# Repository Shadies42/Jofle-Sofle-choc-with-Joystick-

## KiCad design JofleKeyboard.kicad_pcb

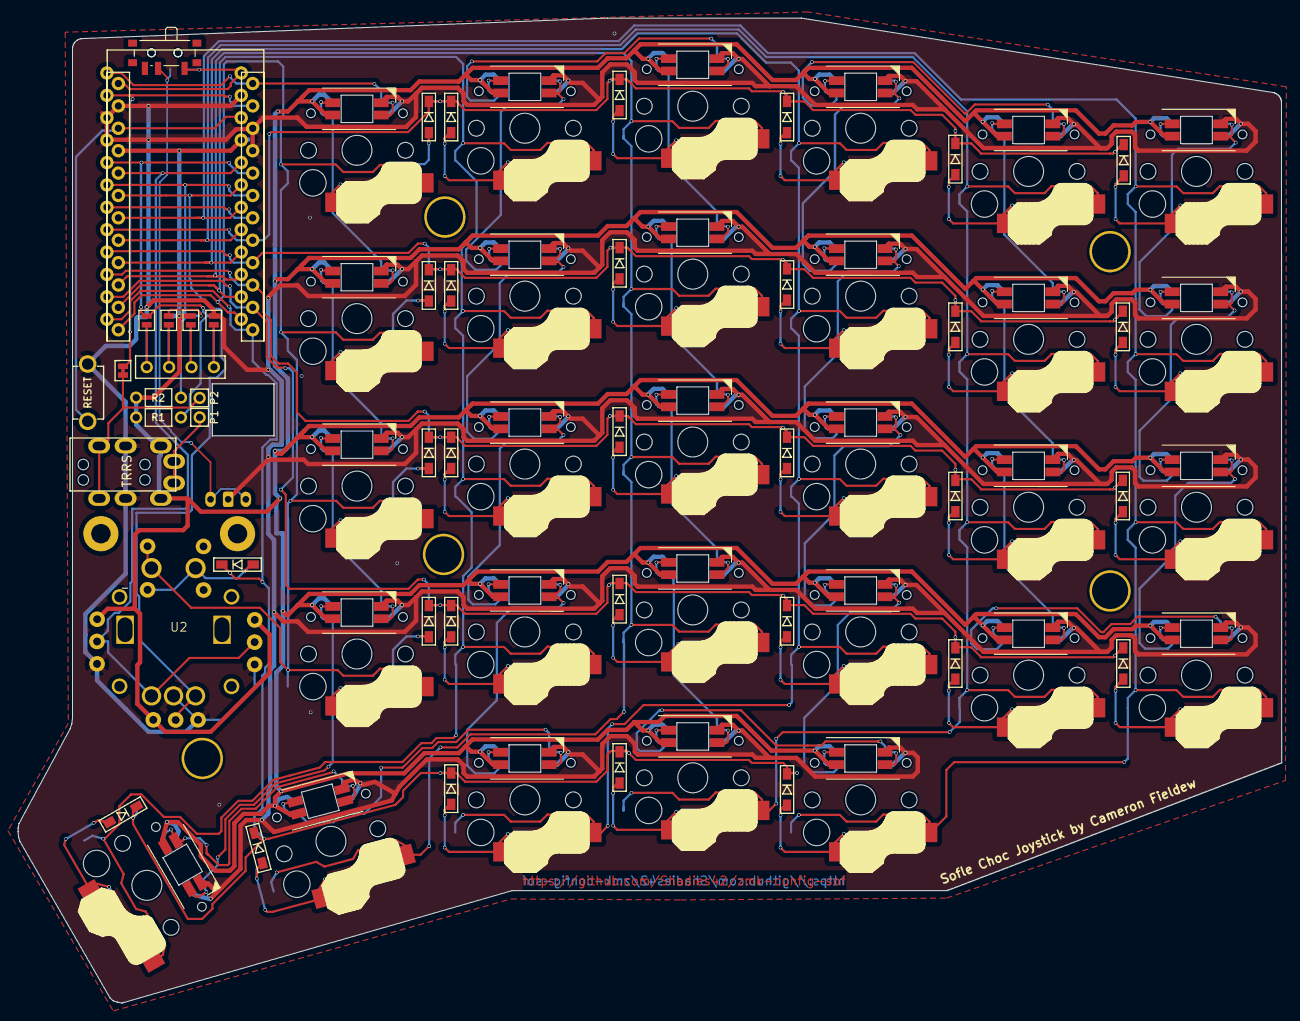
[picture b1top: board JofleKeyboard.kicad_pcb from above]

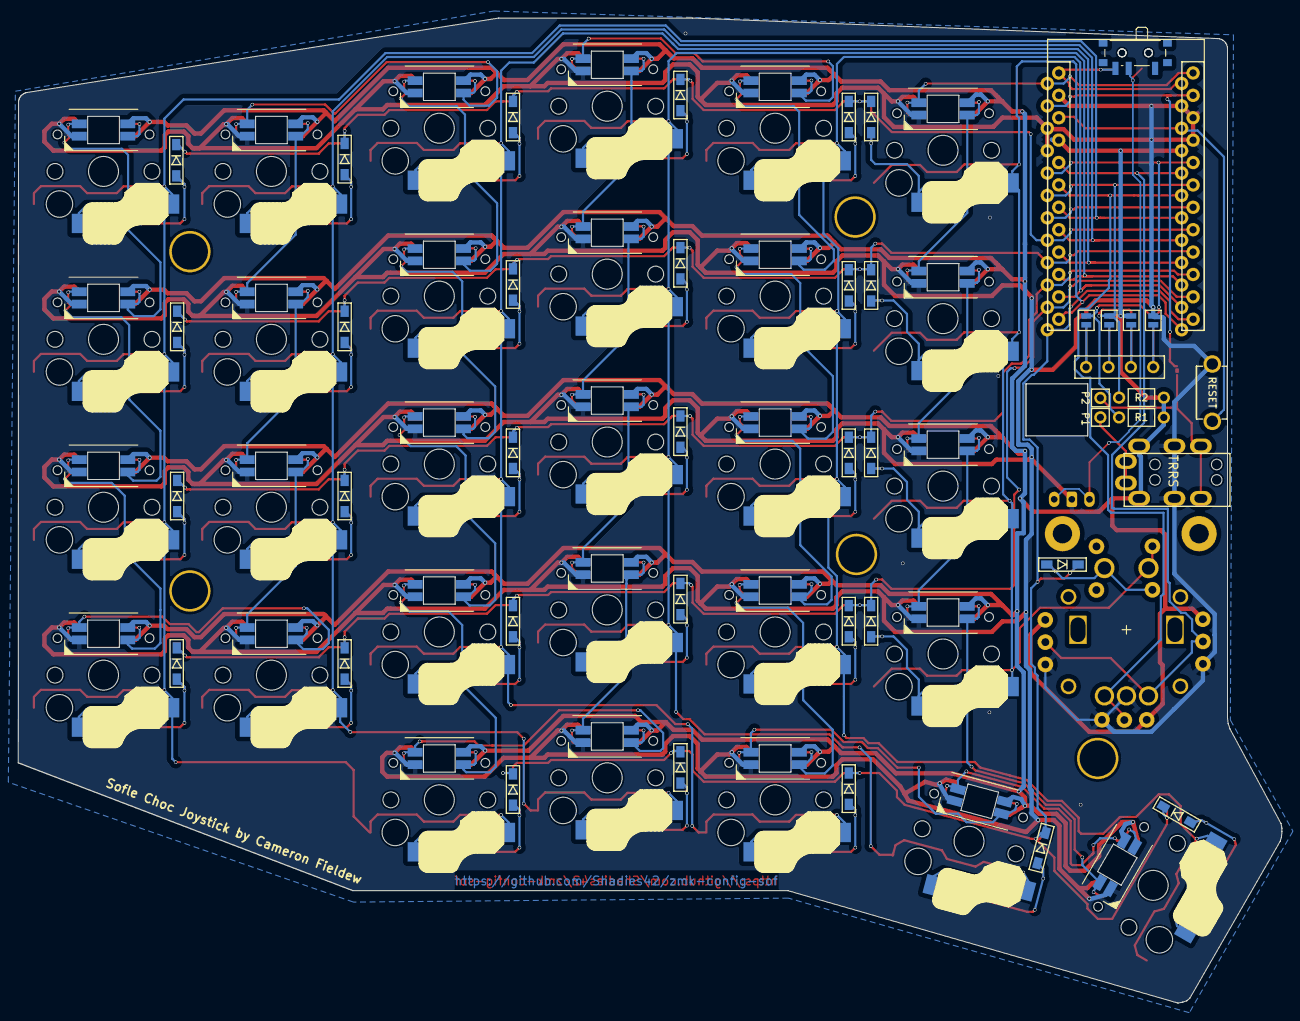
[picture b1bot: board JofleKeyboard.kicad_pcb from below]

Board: 2 copper layers, 143.4 x 111.8 mm, 88 parts (5 on the bottom side), 87 nets.

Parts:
D1, D2, D3, D4, D5, D6, D7, D8, D9, D10, D11, D12, D13, D14, D15, D16, D17, D18, D19, D20, D21, D22, D23, D24, D25, D26, D27, D28, D29, D30: D; crkbd-diode
J2: 4PIN; MJ-4PP-9
J3: OLED; OLED_4Pin
JP1, JP2, JP3, JP4, JP5, JP6, JP7, JP8: Jumper_NO_Small; Jumper
JST_BATT2: Conn_01x02; JST_PH_S2B-PH-K_1x02_P2.00mm_DoubleSided
P1, P2: i2c_pin; 1pin_conn
R1, R2: R; RESISTOR_mini
RSW1: SW_RST; TACT_SWITCH_TVBP06
SW1, SW2, SW3, SW4, SW5, SW6, SW7, SW8, SW9, SW10, SW11, SW12, SW13, SW14, SW15, SW16, SW17, SW18, SW19, SW20, SW21, SW22, SW23, SW24, SW26, SW27, SW28, SW29, SW30: SW_PUSH_LED; Choc_Hotswap_SK6812MiniE
SW31: Rotary_Encoder_Switch; RotaryEncoder_Alps_EC11E-Switch_Vertical_H20mm-keebio_modif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
SW_BATT+1, SW_BATT+2: SW_SPST; SW_SPDT_PCM12
TH1, TH2: HOLE; M2_HOLE_PCB
TH3, TH4, TH5, TH6, TH7: HOLE; HOLE_M2_TH
U1: ProMicro
U2: Joystick
W1: jumper; jumper_data

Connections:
/i2c_c: J2.4, P1.1
/i2c_d: J2.3, P2.1, W1.2
Battery+: JST_BATT2.2, SW_BATT+1.2 (B), SW_BATT+2.2 (B)
DATA: U1.2 (RX(PD2)), W1.1
ENCA: SW31.A, U1.20 (A3(PF4)), U2.V2 (V)
ENCB: SW31.B, U1.19 (A2(PF5)), U2.H2 (H)
GND: J2.2, JP1.2, JP8.2, JST_BATT2.1, RSW1.1, SW1.3 (GND), SW2.3 (GND), SW3.3 (GND), SW4.3 (GND), SW5.3 (GND), SW6.3 (GND), SW7.3 (GND), SW8.3 (GND), SW9.3 (GND), SW10.3 (GND), SW11.3 (GND), SW12.3 (GND), SW13.3 (GND), SW14.3 (GND), SW15.3 (GND), SW16.3 (GND), SW17.3 (GND), SW18.3 (GND), SW19.3 (GND), SW20.3 (GND), SW21.3 (GND), SW22.3 (GND), SW23.3 (GND), SW24.3 (GND), SW26.3 (GND), SW27.3 (GND), SW28.3 (GND), SW29.3 (GND), SW30.3 (GND), SW31.C, U1.3 (GND), U1.4 (GND), U1.23 (GND), U2.H3 (H-), U2.V3 (V-)
LED: SW1.4 (DIN), U1.1 (TX(PD3))
unnamed: D1.2 (A), SW1.5
unnamed: D2.2 (A), SW2.5
unnamed: D3.2 (A), SW3.5
unnamed: D4.2 (A), SW4.5
unnamed: D5.2 (A), SW5.5
unnamed: D6.2 (A), SW6.5
unnamed: D7.2 (A), SW7.5
unnamed: D8.2 (A), SW8.5
unnamed: D9.2 (A), SW9.5
unnamed: D10.2 (A), SW10.5
unnamed: D11.2 (A), SW11.5
unnamed: D12.2 (A), SW12.5
unnamed: D13.2 (A), SW13.5
unnamed: D14.2 (A), SW14.5
unnamed: D15.2 (A), SW15.5
unnamed: D16.2 (A), SW16.5
unnamed: D17.2 (A), SW17.5
unnamed: D18.2 (A), SW18.5
unnamed: D19.2 (A), SW19.5
unnamed: D20.2 (A), SW20.5
unnamed: D21.2 (A), SW21.5
unnamed: D22.2 (A), SW22.5
unnamed: D23.2 (A), SW23.5
unnamed: D24.2 (A), SW24.5
unnamed: D26.2 (A), SW26.5
unnamed: D27.2 (A), SW27.5
unnamed: D28.2 (A), SW28.5
unnamed: D29.2 (A), SW29.5
unnamed: D30.2 (A), SW30.5
unnamed: J3.1, JP4.1, JP8.1
unnamed: J3.2, JP3.1, JP7.1
unnamed: J3.3, JP2.1, JP6.1
unnamed: J3.4, JP1.1, JP5.1
unnamed: SW1.2 (DOUT), SW7.4 (DIN)
unnamed: SW2.4 (DIN), SW8.2 (DOUT)
unnamed: SW2.2 (DOUT), SW3.4 (DIN)
unnamed: SW3.2 (DOUT), SW9.4 (DIN)
unnamed: SW4.2 (DOUT), SW5.4 (DIN)
unnamed: SW10.4 (DIN), SW16.2 (DOUT)
unnamed: SW4.4 (DIN), SW10.2 (DOUT)
unnamed: SW5.2 (DOUT), SW11.4 (DIN)
unnamed: SW11.2 (DOUT), SW17.4 (DIN)
unnamed: SW12.4 (DIN), SW18.2 (DOUT)
unnamed: SW6.4 (DIN), SW12.2 (DOUT)
unnamed: SW7.2 (DOUT), SW13.4 (DIN)
unnamed: SW13.2 (DOUT), SW19.4 (DIN)
unnamed: SW14.4 (DIN), SW20.2 (DOUT)
unnamed: SW8.4 (DIN), SW14.2 (DOUT)
unnamed: SW9.2 (DOUT), SW15.4 (DIN)
unnamed: SW15.2 (DOUT), SW21.4 (DIN)
unnamed: SW16.4 (DIN), SW22.2 (DOUT)
unnamed: SW17.2 (DOUT), SW23.4 (DIN)
unnamed: SW18.4 (DIN), SW24.2 (DOUT)
unnamed: SW19.2 (DOUT), SW26.4 (DIN)
unnamed: SW20.4 (DIN), SW28.2 (DOUT)
unnamed: SW21.2 (DOUT), SW29.4 (DIN)
unnamed: SW22.4 (DIN), SW30.2 (DOUT)
unnamed: SW23.2 (DOUT), SW24.4 (DIN)
unnamed: SW26.2 (DOUT), SW27.4 (DIN)
unnamed: SW27.2 (DOUT), SW28.4 (DIN)
unnamed: SW29.2 (DOUT), SW30.4 (DIN)
unnamed: U2.S1 (SHIELD), U2.S2 (SHIELD), U2.S3 (SHIELD), U2.S4 (SHIELD)
RESET: RSW1.2, U1.22 (RST)
SCL: JP3.2, JP6.2, R2.2, U1.6 (SCL(PD0))
SDA: JP4.2, JP5.2, R1.2, U1.5 (SDA(PD1))
SW25A: SW1.6, SW7.6, SW13.6, SW19.6, SW31.S2, U1.13 (D10(PB6)), U2.B1A (SEL+)
SW25B: D25.2 (A), SW31.S1, U2.B2A (SEL-)
VCC: J2.1, JP2.2, JP7.2, R1.1, R2.1, SW1.1 (VDD), SW2.1 (VDD), SW3.1 (VDD), SW4.1 (VDD), SW5.1 (VDD), SW6.1 (VDD), SW7.1 (VDD), SW8.1 (VDD), SW9.1 (VDD), SW10.1 (VDD), SW11.1 (VDD), SW12.1 (VDD), SW13.1 (VDD), SW14.1 (VDD), SW15.1 (VDD), SW16.1 (VDD), SW17.1 (VDD), SW18.1 (VDD), SW19.1 (VDD), SW20.1 (VDD), SW21.1 (VDD), SW22.1 (VDD), SW23.1 (VDD), SW24.1 (VDD), SW26.1 (VDD), SW27.1 (VDD), SW28.1 (VDD), SW29.1 (VDD), SW30.1 (VDD), U1.21 (VCC), U2.H1 (H+), U2.V1 (V+)
col0: SW6.6, SW12.6, SW18.6, SW24.6, SW30.6, U1.18 (A1(PF6))
col1: SW5.6, SW11.6, SW17.6, SW23.6, SW29.6, U1.17 (A0(PF7))
col2: SW4.6, SW10.6, SW16.6, SW22.6, SW28.6, U1.16 (D15(PB1))
col3: SW3.6, SW9.6, SW15.6, SW21.6, SW27.6, U1.15 (D14(PB3))
col4: SW2.6, SW8.6, SW14.6, SW20.6, SW26.6, U1.14 (D16(PB2))
raw: SW_BATT+1.1 (A), SW_BATT+2.1 (A), U1.24 (RAW)
row0: D1.1 (K), D2.1 (K), D3.1 (K), D4.1 (K), D5.1 (K), D6.1 (K), U1.8 (D5(PC6))
row1: D7.1 (K), D8.1 (K), D9.1 (K), D10.1 (K), D11.1 (K), D12.1 (K), U1.9 (D6(PD7))
row2: D13.1 (K), D14.1 (K), D15.1 (K), D16.1 (K), D17.1 (K), D18.1 (K), U1.10 (D7(PE6))
row3: D19.1 (K), D20.1 (K), D21.1 (K), D22.1 (K), D23.1 (K), D24.1 (K), U1.11 (D8(PB4))
row4: D25.1 (K), D26.1 (K), D27.1 (K), D28.1 (K), D29.1 (K), D30.1 (K), U1.12 (D9(PB5))
